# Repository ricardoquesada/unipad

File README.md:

# Unipad™

Wireless Bluetooth Gamepad, Paddle & Mouse adapters for vintage 8-bit and 16-bit computers — by the creator of [Unijoysticle](https://github.com/ricardoquesada/unijoysticle2) and [Bluepad32](https://github.com/ricardoquesada/bluepad32).

## Models

| Model | Target Systems | Wireless Inputs | Power Draw | Hardware Folder | Firmware Folder |
| :--- | :--- | :--- | :--- | :--- | :--- |
| **Unipad C64** *(Rev. A)* | Commodore 64 / 128 | Bluetooth Gamepads, **1351 Analog Mouse**, **1311/1312 Paddles**, Rumble | `< 45 mA` (CIA/SID-protected) | [`hardware/unipad_c64/`](hardware/unipad_c64/) | [`firmware/unipad_c64/`](firmware/unipad_c64/) |

## Repository Structure

This monorepo houses the complete hardware, firmware, 3D enclosure, and documentation stack for the **Unipad** product family:

```text
unipad/
├── hardware/               # KiCad 10 schematics, 4-layer PCBs, shared libraries & JLCPCB bundles
│   ├── libs/Unipad.pretty/ # Shared KiCad footprints across all Unipad boards
│   └── unipad_c64/         # Unipad C64 (Rev. A) KiCad 10 project & JLCPCB Gerbers/BOM/CPL
├── firmware/               # RP2350 (Pico 2 W) firmware + PIO state machines
│   ├── external/           # Upstream git submodules (e.g. bluepad32)
│   ├── common/             # Shared Unipad RP2350 drivers & helpers
│   └── unipad_c64/         # Unipad C64 platform target, GPIO map & PIO programs
├── case/                   # 3D-printable enclosures (STEP / STL)
│   └── unipad_c64/         # Unipad C64 enclosure specs & CAD files
└── docs/                   # User guides & exported schematic PDFs
    └── schematics/         # Exported PDF schematics (e.g. schematic_unipad_c64.pdf)
```

## Key Highlights (Unipad C64)

- **3-in-1 C64 Control Port Support:** Use modern Bluetooth gamepads (DualSense, Xbox, Switch Pro, 8BitDo, etc.), Bluetooth mice (**Commodore 1351 analog mode**), and analog sticks/controllers as **Commodore 1311/1312 Paddles** across both Control Ports.
- **Deterministic RP2350 PIO Timing:** Dedicated 150 MHz Programmable I/O (PIO) hardware state machines synchronize directly to the C64 SID `POTX`/`POTY` discharge cycle with zero CPU interrupt jitter and automatic PAL/NTSC clock calibration.
- **Low-Power & Vintage-Safe:** Draws `< 45 mA` from the C64 `+5V` rail (less than half of ESP32-based adapters), protected by a `250 mA` resettable PTC polyfuse, ferrite Pi-filter, zero-drop `DMG2305UX` P-FET ideal diode (preventing USB `VBUS` back-feeding into the C64), `74HCT05` open-drain buffers, and 5V fail-safe SID `SYNC` dividers.
- **5-Second Drag-and-Drop Updates:** Hold `BOOTSEL`, plug into USB, and drop a `.uf2` firmware file onto the drive — no serial drivers required.

## License

All hardware designs (`hardware/`), 3D enclosures (`case/`), and documentation (`docs/`) are licensed under **Creative Commons Attribution-NonCommercial-ShareAlike 4.0 International ([CC BY-NC-SA 4.0](LICENSE))**. Third-party submodules under `firmware/external/` retain their respective upstream licenses.

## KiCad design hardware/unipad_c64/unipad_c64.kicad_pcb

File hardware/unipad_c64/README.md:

# Unipad™ C64 (Rev. A)

**Unipad C64** is a low-power (`< 45 mA`), CIA/SID-protected wireless Bluetooth adapter for the Commodore 64 and Commodore 128, supporting modern Bluetooth **Gamepads**, **Commodore 1351 Analog Mice**, **Commodore 1311/1312 Paddles**, and **Rumble**.

## Schematic

* [Unipad C64 Schematic (PDF)](../../docs/schematics/schematic_unipad_c64.pdf)

## Layout & Fabrication

* Schematic and 4-layer PCB layout files are in **KiCad 10** format in this folder (`F.Cu`, `In1.Cu` GND, `In2.Cu` Power, `B.Cu`).
* Shared custom footprints resolve from [`../libs/Unipad.pretty/`](../libs/Unipad.pretty/).
* Turnkey JLCPCB 4-layer Gerbers, Excellon drill files, BOM, and Pick-and-Place CPL are located in [`gerber_jlcpcb_rev_a/`](gerber_jlcpcb_rev_a/).
* **Hardware Board ID (`BOARD_ID[2:0] = 0b111`)**: Three zero-BOM open copper solder jumpers **`JP1` (`ID0` / `GP26`)**, **`JP2` (`ID1` / `GP27`)**, and **`JP3` (`ID2` / `GP28`)** are placed on `B.Cu` beneath `U1` Pins 31–34 (excluded from BOM and CPL; left `OPEN` by default for `Unipad C64`).

## Bill of Materials (BOM)

| Item | Qty | Reference(s) | Value | LibPart | Footprint | LCSC |
| ---- | --- | ------------ | ----- | ------- | --------- | ---- |
| 1 | 7 | C1, C4, C8, C10, C11, C12, C13 | .1uF | Device:C_Small | Capacitor_SMD:C_0805_2012Metric_Pad1.18x1.45mm_HandSolder | C49678 |
| 2 | 3 | C5, C6, C9 | 10uF | Device:C_Small | Capacitor_SMD:C_0805_2012Metric_Pad1.18x1.45mm_HandSolder | C15850 |
| 3 | 1 | C7 | 47uF | Device:C_Small | Capacitor_SMD:C_0805_2012Metric_Pad1.18x1.45mm_HandSolder | C124129 |
| 4 | 1 | D1 | PWR | Device:LED | LED_SMD:LED_0805_2012Metric_Pad1.15x1.40mm_HandSolder | C2297 |
| 5 | 1 | D4 | BLUE | Device:LED | LED_SMD:LED_0805_2012Metric_Pad1.15x1.40mm_HandSolder | C84259 |
| 6 | 1 | D5 | GREEN | Device:LED | LED_SMD:LED_0805_2012Metric_Pad1.15x1.40mm_HandSolder | C2297 |
| 7 | 1 | D6 | RED | Device:LED | LED_SMD:LED_0805_2012Metric_Pad1.15x1.40mm_HandSolder | C84256 |
| 8 | 1 | F1 | 250mA_PTC | Device:Polyfuse_Small | Fuse:Fuse_0805_2012Metric | C20608679 |
| 9 | 1 | FB1 | 600R@100MHz | Device:FerriteBead_Small | Inductor_SMD:L_0805_2012Metric | C1017 |
| 10 | 2 | H1, H2 | MountingHole_Pad | Mechanical:MountingHole_Pad | MountingHole:MountingHole_3.2mm_M3_Pad_Via | ~ |
| 11 | 1 | J2 | PORT #1 | Connector:DB9_Female | Connector_Dsub:DSUB-9_Socket_Horizontal_P2.77x2.54mm_EdgePinOffset9.40mm | ~ |
| 12 | 1 | J3 | PORT #2 | Connector:DB9_Female | Connector_Dsub:DSUB-9_Socket_Horizontal_P2.77x2.54mm_EdgePinOffset9.40mm | ~ |
| 13 | 1 | J4 | DEBUG_LA_HDR | Connector_Generic:Conn_01x08 | Connector_PinHeader_2.54mm:PinHeader_1x08_P2.54mm_Vertical | ~ |
| 14 | 1 | Q1 | DMG2305UX | Transistor_FET:TP0610T | Package_TO_SOT_SMD:SOT-23 | C144153 |
| 15 | 9 | R1, R10, R11, R13, R14, R16, R17, R19, R22 | 10K | Device:R | Resistor_SMD:R_0805_2012Metric_Pad1.20x1.40mm_HandSolder | C17414 |
| 16 | 4 | R2, R7, R8, R9 | 3K3 | Device:R | Resistor_SMD:R_0805_2012Metric_Pad1.20x1.40mm_HandSolder | C26010 |
| 17 | 1 | R3 | 100K | Device:R | Resistor_SMD:R_0805_2012Metric_Pad1.20x1.40mm_HandSolder | C149504 |
| 18 | 2 | R20, R23 | 22K | Device:R | Resistor_SMD:R_0805_2012Metric_Pad1.20x1.40mm_HandSolder | C17560 |
| 19 | 1 | SW1 | RESET | Switch:SW_Push | Button_Switch_THT:SW_Tactile_SPST_Angled_PTS645Vx39-2LFS | ~ |
| 20 | 1 | SW3 | MODE | Switch:SW_Push | Button_Switch_THT:SW_Tactile_SPST_Angled_PTS645Vx39-2LFS | ~ |
| 21 | 1 | SW4 | SWAP | Switch:SW_Push | Button_Switch_THT:SW_Tactile_SPST_Angled_PTS645Vx39-2LFS | ~ |
| 22 | 1 | U1 | Raspberry_Pi_Pico_2_W | Pico_1 | Unipad:RPi_Pico_2_W_SMD_TH | ~ |
| 23 | 3 | U4, U5, U6 | 74HCT05 | 74xx:74LS05 | Package_SO:SOIC-14_3.9x8.7mm_P1.27mm | C49188197 |

## License

Licensed under [CC BY-NC-SA 4.0](../../LICENSE).

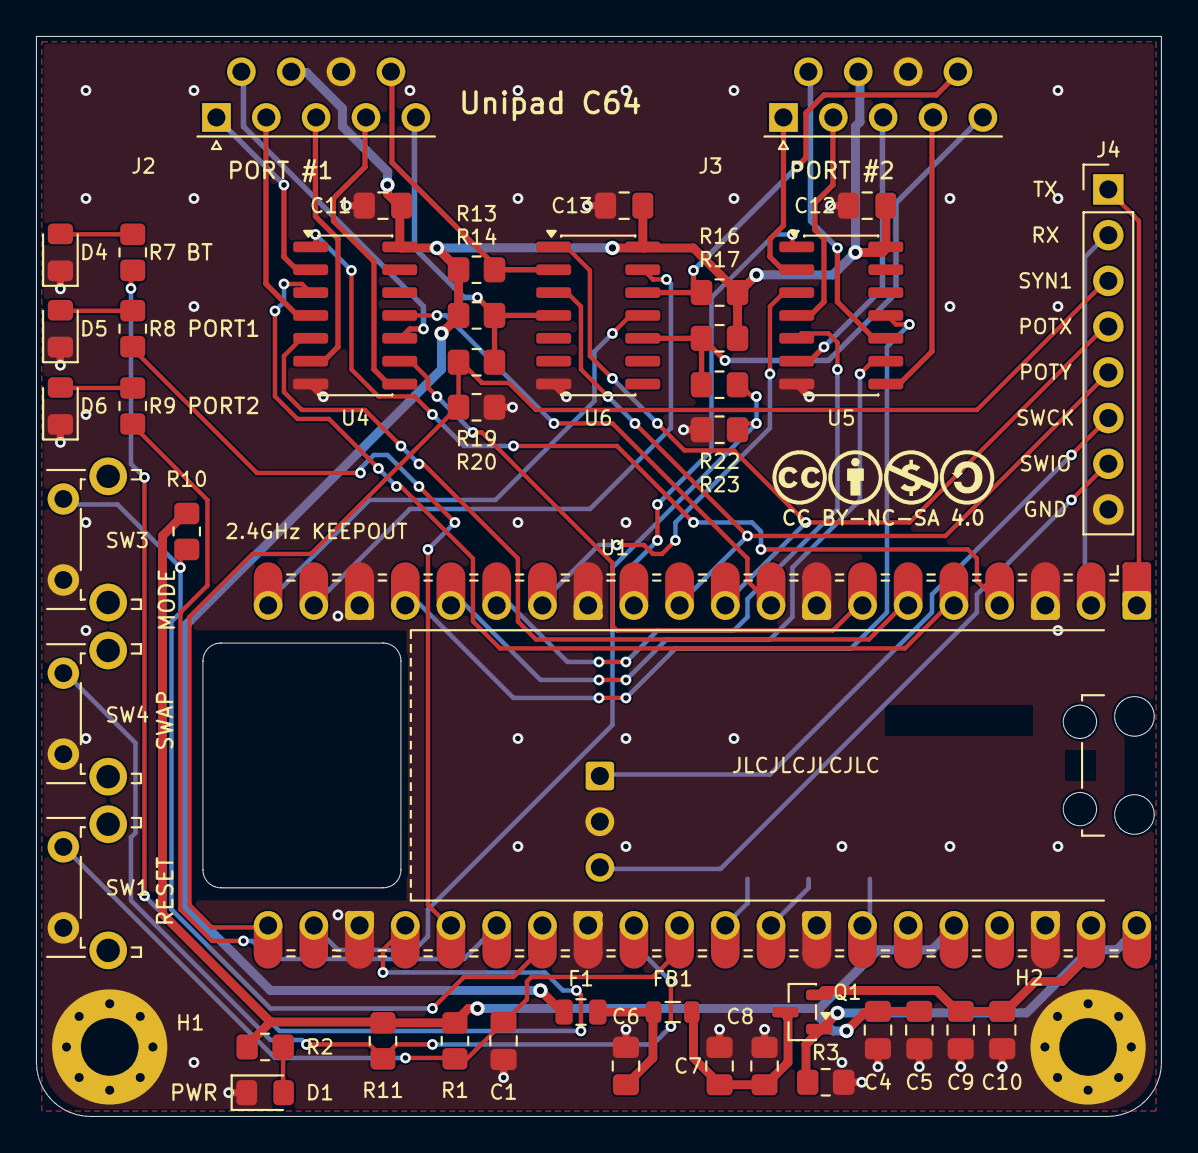
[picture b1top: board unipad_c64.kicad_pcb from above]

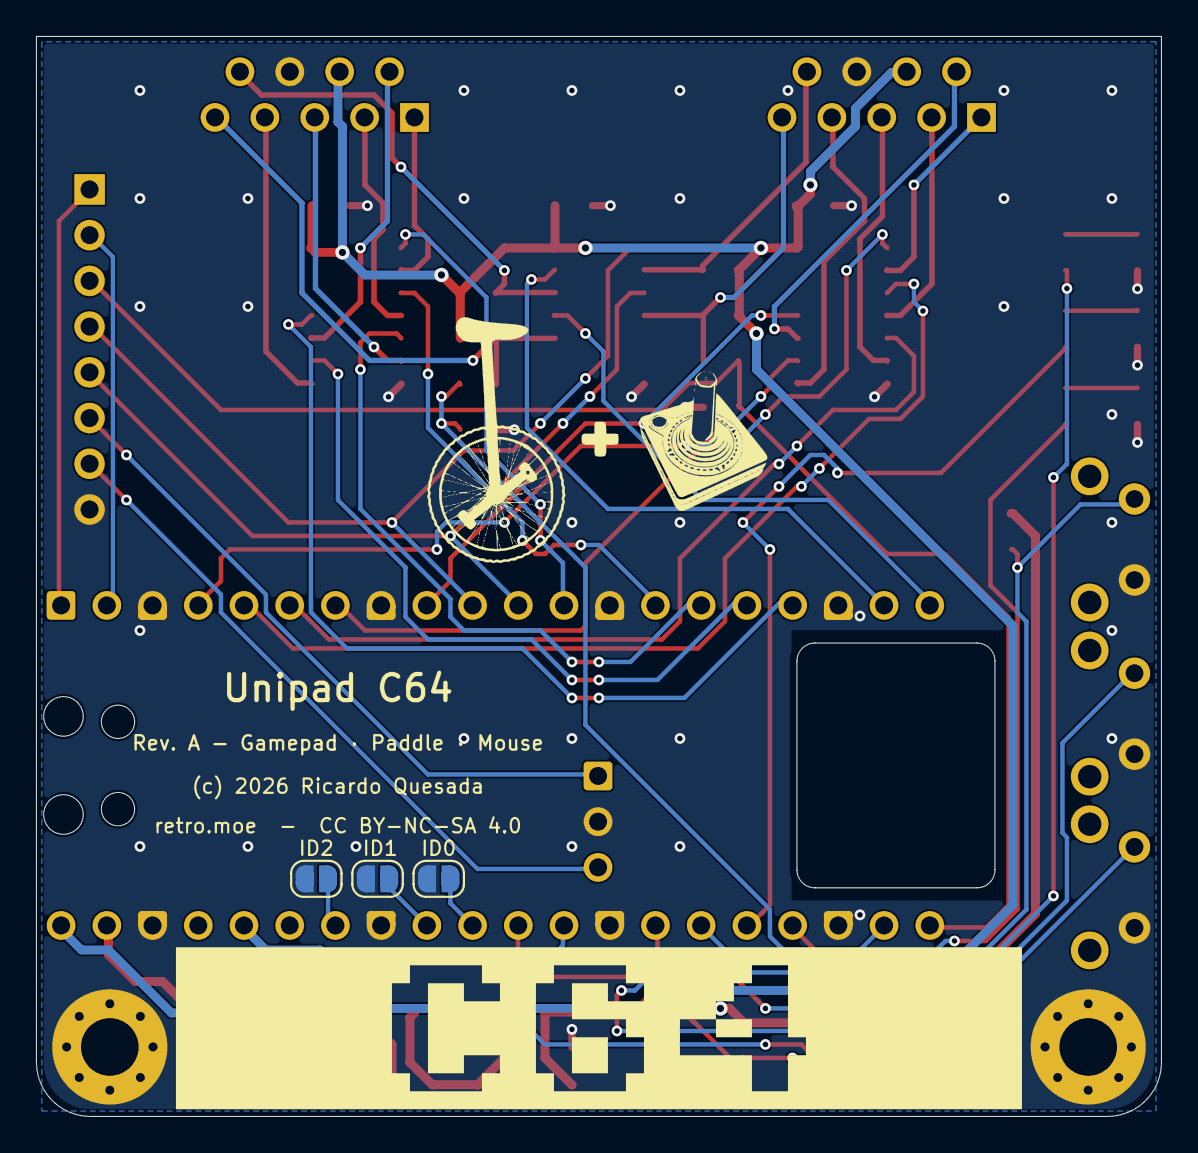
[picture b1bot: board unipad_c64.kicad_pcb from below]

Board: 4 copper layers, 62.5 x 60.0 mm, 51 parts (4 on the bottom side), 54 nets.

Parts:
C1, C4, C8, C10, C11, C12, C13: .1uF; C_0805_2012Metric_Pad1.18x1.45mm_HandSolder
C5, C6, C9: 10uF; C_0805_2012Metric_Pad1.18x1.45mm_HandSolder
C7: 47uF; C_0805_2012Metric_Pad1.18x1.45mm_HandSolder
D1: PWR; LED_0805_2012Metric_Pad1.15x1.40mm_HandSolder
D4: BLUE; LED_0805_2012Metric_Pad1.15x1.40mm_HandSolder
D5: GREEN; LED_0805_2012Metric_Pad1.15x1.40mm_HandSolder
D6: RED; LED_0805_2012Metric_Pad1.15x1.40mm_HandSolder
F1: 250mA_PTC; Fuse_0805_2012Metric
FB1: 600R@100MHz; L_0805_2012Metric
H1, H2: MountingHole_Pad; MountingHole_3.2mm_M3_Pad_Via
J2: PORT JOY #1; DSUB-9_Socket_Horizontal_P2.77x2.54mm_EdgePinOffset9.40mm
J3: PORT JOY #2; DSUB-9_Socket_Horizontal_P2.77x2.54mm_EdgePinOffset9.40mm
J4: DEBUG_LA_HDR; PinHeader_1x08_P2.54mm_Vertical
JP1: ID0; SolderJumper-2_P1.3mm_Open_RoundedPad1.0x1.5mm
JP2: ID1; SolderJumper-2_P1.3mm_Open_RoundedPad1.0x1.5mm
JP3: ID2; SolderJumper-2_P1.3mm_Open_RoundedPad1.0x1.5mm
LOGO1: CC_BY-NC-SA_4.0; CC_BY_NC_SA_4_0_SilkScreen
LOGO2: LOGO; unijoysticle_logo_small
Q1: DMG2305UX; SOT-23
R1, R10, R11, R13, R14, R16, R17, R19, R22: 10K; R_0805_2012Metric_Pad1.20x1.40mm_HandSolder
R2, R7, R8, R9: 3K3; R_0805_2012Metric_Pad1.20x1.40mm_HandSolder
R3: 100K; R_0805_2012Metric_Pad1.20x1.40mm_HandSolder
R20, R23: 22K; R_0805_2012Metric_Pad1.20x1.40mm_HandSolder
SW1: RESET; SW_Tactile_SPST_Angled_PTS645Vx39-2LFS
SW3: MODE; SW_Tactile_SPST_Angled_PTS645Vx39-2LFS
SW4: SWAP; SW_Tactile_SPST_Angled_PTS645Vx39-2LFS
U1: Raspberry_Pi_Pico_2_W; RPi_Pico_2_W_SMD_TH
U4, U5, U6: 74HCT05; SOIC-14_3.9x8.7mm_P1.27mm

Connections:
+3V3: C4.1, C5.1, R1.1, R2.2, R10.1, R11.1, U1.36
+5V: C11.1, C12.1, C13.1, F1.1, J2.7, J3.7, R13.1, R14.1, R16.1, R17.1, U4.14, U5.14, U6.14
/C64 Ports/J1_DOWN: J2.2, U4.4
/C64 Ports/J1_FIRE: J2.6, U4.10
/C64 Ports/J1_LEFT: J2.3, U4.6
/C64 Ports/J1_POTX: J2.9, R13.2, U6.2
/C64 Ports/J1_POTY: J2.5, R14.2, R19.1, U6.4
/C64 Ports/J1_RIGHT: J2.4, U4.8
/C64 Ports/J1_UP: J2.1, U4.2
/C64 Ports/J2_DOWN: J3.2, U5.4
/C64 Ports/J2_FIRE: J3.6, U5.10
/C64 Ports/J2_LEFT: J3.3, U5.6
/C64 Ports/J2_POTX: J3.9, R16.2, U6.12
/C64 Ports/J2_POTY: J3.5, R17.2, R22.1, U6.10
/C64 Ports/J2_RIGHT: J3.4, U5.8
/C64 Ports/J2_UP: J3.1, U5.2
/Pico 2 W & Debug/BOARD_ID0: JP1.1, U1.31
/Pico 2 W & Debug/BOARD_ID1: JP2.1, U1.32
/Pico 2 W & Debug/BOARD_ID2: JP3.1, U1.34
/Pico 2 W & Debug/PICO_RUN: C1.2, R1.2, SW1.2, U1.30
/Pico 2 W & Debug/SWCLK: J4.6, U1.41
/Pico 2 W & Debug/SWDIO: J4.7, U1.43
/Power & Filtering/+5V_FILT: C7.1, C8.1, FB1.2, Q1.3
/Power & Filtering/+5V_FUSED: C6.1, F1.2, FB1.1
GND: C1.1, C4.2, C5.2, C6.2, C7.2, C8.2, C9.2, C10.2, C11.2, C12.2, C13.2, D1.1, D4.1, D5.1, D6.1, H1.1, H2.1, J2.8, J3.8, J4.8, JP1.2, JP2.2, JP3.2, R3.2, R20.2, R23.2, SW1.1, SW3.1, SW4.1, U1.3, U1.8, U1.13, U1.18, U1.23, U1.28, U1.33, U1.38, U1.42, U4.7, U5.7, U6.7
GPIO_J1_DOWN: U1.5, U4.3
GPIO_J1_FIRE: U1.9, U4.11
GPIO_J1_LEFT: U1.6, U4.5
GPIO_J1_POTX: J4.4, U1.10, U6.1
GPIO_J1_POTY: J4.5, U1.11, U6.3
GPIO_J1_RIGHT: U1.7, U4.9
GPIO_J1_UP: U1.4, U4.1
GPIO_J2_DOWN: U1.14, U5.3
GPIO_J2_FIRE: U1.17, U5.11
GPIO_J2_LEFT: U1.15, U5.5
GPIO_J2_POTX: U1.19, U6.13
GPIO_J2_POTY: U1.20, U6.11
GPIO_J2_RIGHT: U1.16, U5.9
GPIO_J2_UP: U1.12, U5.1
GPIO_LED_BT: R7.2, U1.24
GPIO_LED_J1: R8.2, U1.25
GPIO_LED_J2: R9.2, U1.26
GPIO_SWITCH_MODE: R10.2, SW3.2, U1.27
GPIO_SWITCH_SWAP: R11.2, SW4.2, U1.29
GPIO_SYNC_J1: J4.3, R19.2, R20.1, U1.21
GPIO_SYNC_J2: R22.2, R23.1, U1.22
GPIO_UART_RX: J4.2, U1.2
GPIO_UART_TX: J4.1, U1.1
unnamed: D1.2, R2.1
unnamed: D4.2, R7.1
unnamed: D5.2, R8.1
unnamed: D6.2, R9.1
VBUS: Q1.1, R3.1, U1.40
VSYS: C9.1, C10.1, Q1.2, U1.39

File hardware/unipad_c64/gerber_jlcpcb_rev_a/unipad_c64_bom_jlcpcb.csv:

"Comment","Designator","Footprint","LCSC","MPN","Manufacturer"
".1uF","C1,C4,C8,C10,C11,C12,C13","Capacitor_SMD:C_0805_2012Metric_Pad1.18x1.45mm_HandSolder","C49678","CC0805KRX7R9BB104","YAGEO"
"10uF","C5,C6,C9","Capacitor_SMD:C_0805_2012Metric_Pad1.18x1.45mm_HandSolder","C15850","CL21A106KAYNNNE","Samsung Electro-Mechanics"
"47uF","C7","Capacitor_SMD:C_0805_2012Metric_Pad1.18x1.45mm_HandSolder","C124129","GRM21BR61A476ME15L","Murata Electronics"
"PWR","D1","LED_SMD:LED_0805_2012Metric_Pad1.15x1.40mm_HandSolder","C2297","KT-0805G","Hubei KENTO Elec"
"BLUE","D4","LED_SMD:LED_0805_2012Metric_Pad1.15x1.40mm_HandSolder","C84259","NCD0805B2","Foshan NationStar Optoelectronics"
"GREEN","D5","LED_SMD:LED_0805_2012Metric_Pad1.15x1.40mm_HandSolder","C2297","KT-0805G","Hubei KENTO Elec"
"RED","D6","LED_SMD:LED_0805_2012Metric_Pad1.15x1.40mm_HandSolder","C84256","NCD0805R1","Foshan NationStar Optoelectronics"
"250mA_PTC","F1","Fuse:Fuse_0805_2012Metric","C20608679","0805L025/36XR","LUTE"
"600R@100MHz","FB1","Inductor_SMD:L_0805_2012Metric","C1017","GZ2012D601TF","Sunlord"
"DMG2305UX","Q1","Package_TO_SOT_SMD:SOT-23","C144153","DMG2305UX-13","Diodes Incorporated"
"10K","R1,R10,R11,R13,R14,R16,R17,R19,R22","Resistor_SMD:R_0805_2012Metric_Pad1.20x1.40mm_HandSolder","C17414","0805W8F1002T5E","UNI-ROYAL"
"3K3","R2,R7,R8,R9","Resistor_SMD:R_0805_2012Metric_Pad1.20x1.40mm_HandSolder","C26010","0805W8F3301T5E","UNI-ROYAL"
"100K","R3","Resistor_SMD:R_0805_2012Metric_Pad1.20x1.40mm_HandSolder","C149504","0805W8F1003T5E","UNI-ROYAL"
"22K","R20,R23","Resistor_SMD:R_0805_2012Metric_Pad1.20x1.40mm_HandSolder","C17560","0805W8F2202T5E","UNI-ROYAL"
"74HCT05","U4,U5,U6","Package_SO:SOIC-14_3.9x8.7mm_P1.27mm","C49188197","EM74HCT05D","EnergyMath"

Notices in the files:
hardware/unipad_c64/unipad_c64.kicad_pcb:
License: CC BY-NC-SA 4.0 (Attribution-NonCommercial-ShareAlike 4.0)
(c) 2026 Ricardo Quesada
retro.moe  -  CC BY-NC-SA 4.0
parts and their libraries:
Creative Commons Attribution-NonCommercial-ShareAlike 4.0 International (CC BY-NC-SA 4.0) Silkscreen Badge
https://creativecommons.org/licenses/by-nc-sa/4.0
